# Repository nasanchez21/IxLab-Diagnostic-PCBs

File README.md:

# IxLab-Diagnostic-PCBs
A repository for various hardware diagnostic circuits for testing/maintaining Ix Lab materials

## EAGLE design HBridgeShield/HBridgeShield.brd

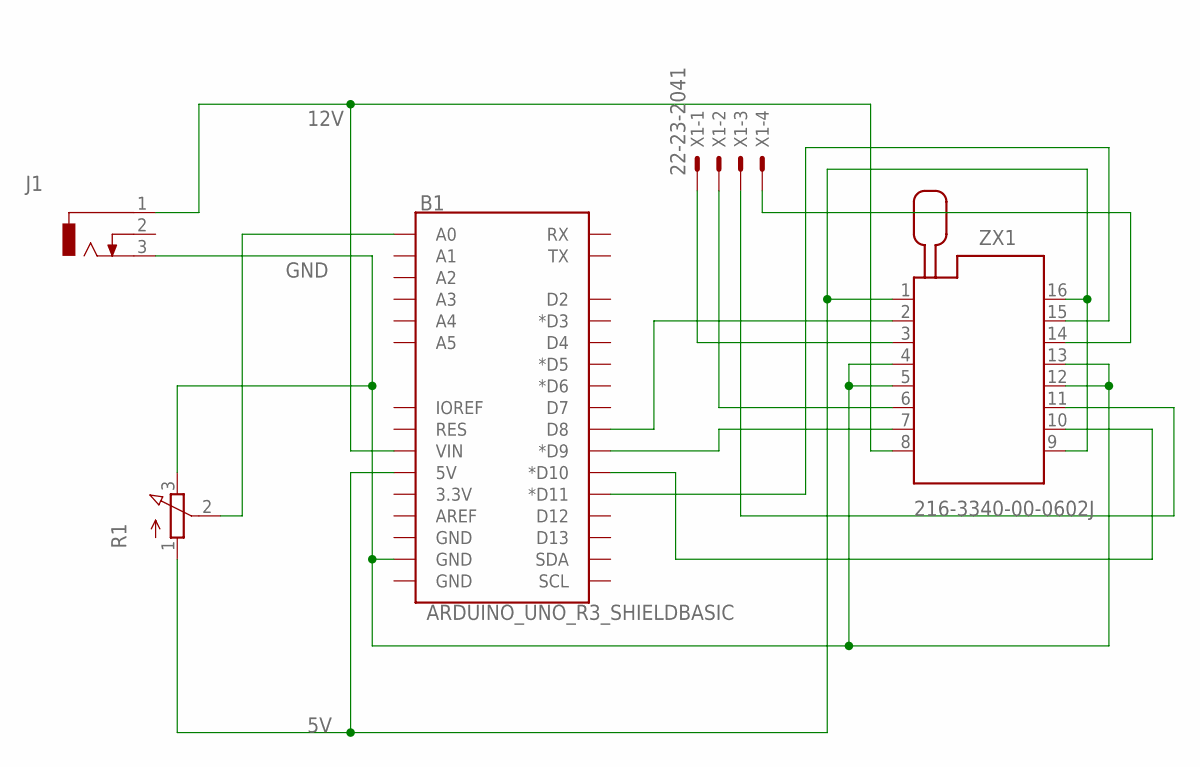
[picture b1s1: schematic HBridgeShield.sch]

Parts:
B1: ARDUINO_UNO_R3_SHIELDBASIC; UNO_R3_SHIELD
J1: DCJ0303
R1: 3RP/1610N
X1: 22-23-2041
ZX1: 216-3340-00-0602J

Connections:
5V: B1.5V, R1.1 (A), ZX1.1, ZX1.9, ZX1.16
12V: B1.VIN, J1.1, ZX1.8
GND: B1.GND@1 (GND), J1.3, R1.3 (E), ZX1.4, ZX1.5, ZX1.12, ZX1.13
unnamed: B1.D9 (*D9), ZX1.7
unnamed: B1.D10 (*D10), ZX1.10
unnamed: B1.D8, ZX1.2
unnamed: B1.D11 (*D11), ZX1.15
unnamed: X1.1, ZX1.3
unnamed: B1.A0, R1.2 (S)
unnamed: X1.2, ZX1.6
unnamed: X1.4, ZX1.14
unnamed: X1.3, ZX1.11

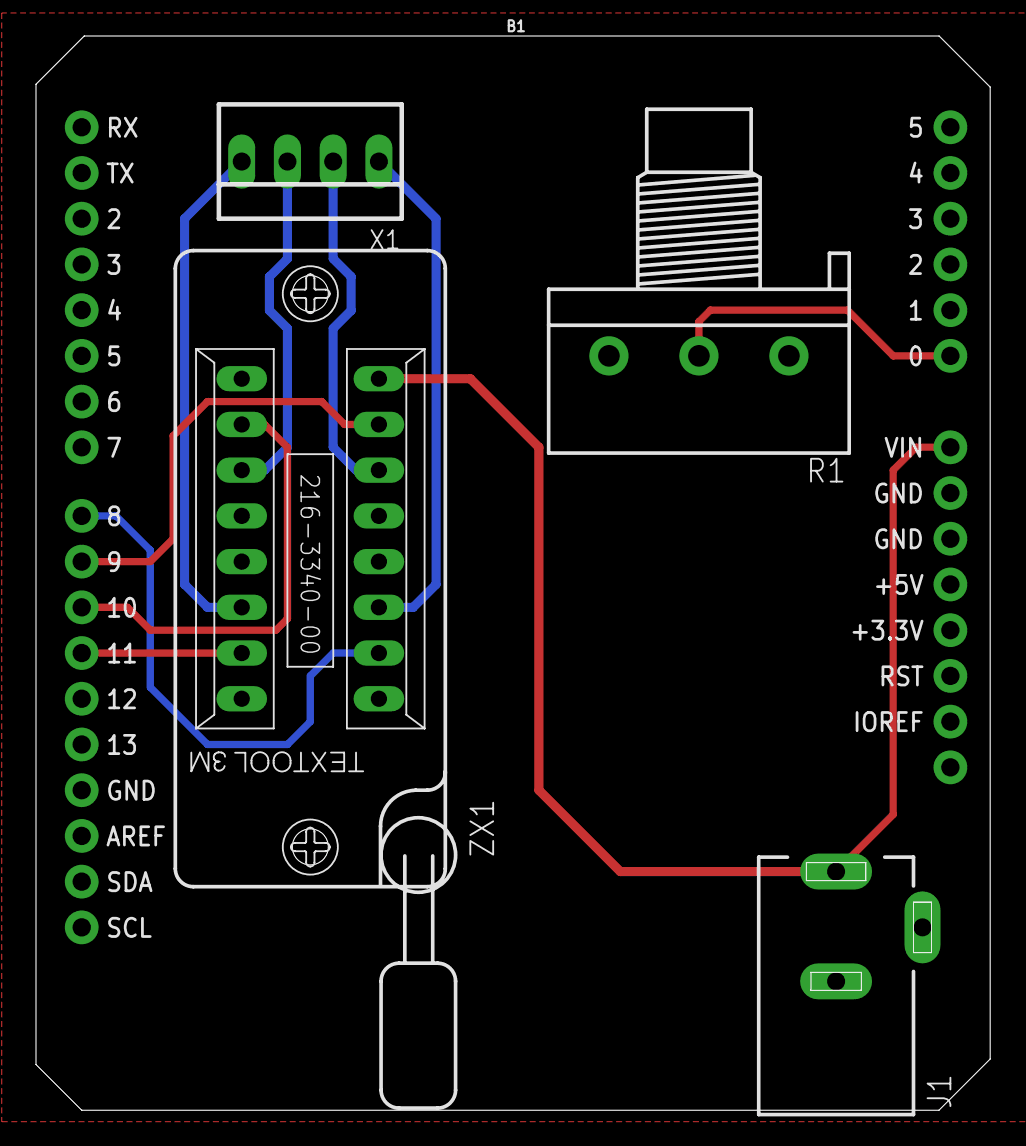
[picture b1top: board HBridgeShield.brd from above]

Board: 2 copper layers, 53.0 x 59.7 mm, 5 parts (0 on the bottom side), 12 nets.

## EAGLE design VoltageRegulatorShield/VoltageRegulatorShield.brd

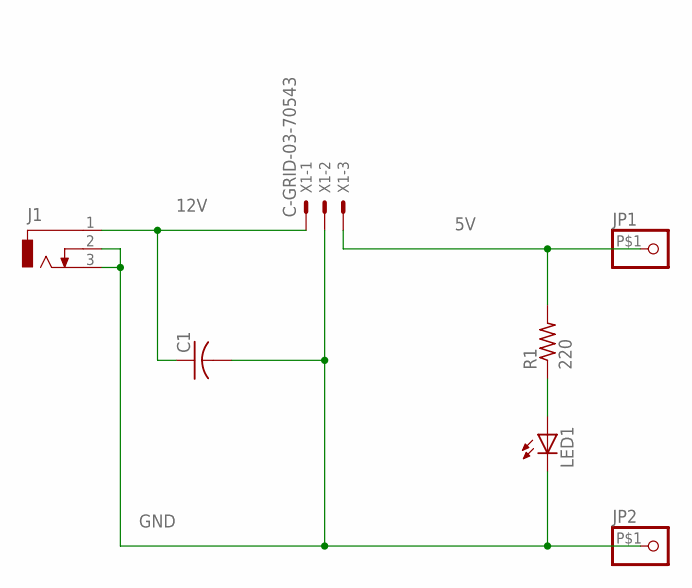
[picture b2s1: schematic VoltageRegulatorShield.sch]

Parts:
C1: C-US025-025X050; C025-025X050
J1: DCJ0303
JP1, JP2: PINHD-1X1-BIGPOGO; 1X1-BIGPOGO
LED1: LED5MM
R1: 220; V234/12
X1: C-GRID-03-70543; 70543-03

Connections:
5V: JP1.P$1, R1.2, X1.3
12V: C1.1, J1.1, X1.1
GND: C1.2, J1.2, J1.3, JP2.P$1, LED1.K (C), X1.2
unnamed: LED1.A, R1.1

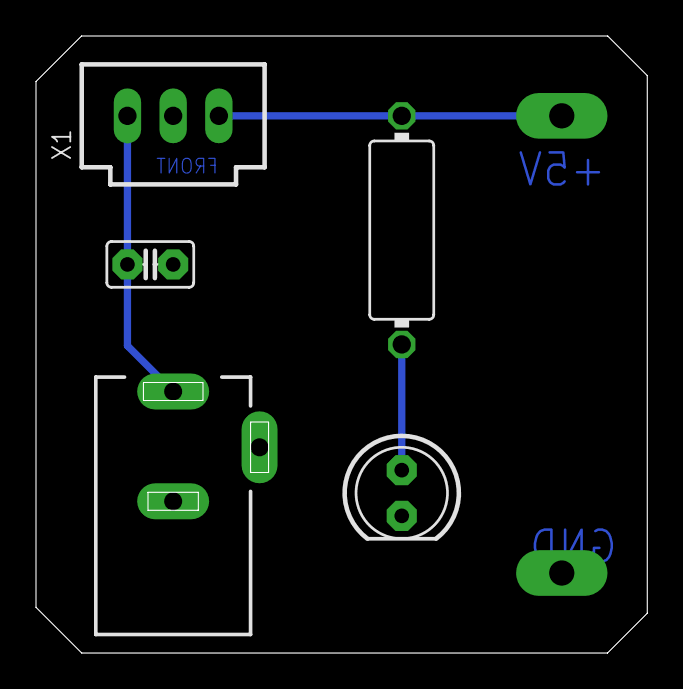
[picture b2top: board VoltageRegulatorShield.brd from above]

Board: 2 copper layers, 34.0 x 34.3 mm, 7 parts (0 on the bottom side), 4 nets.

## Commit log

2019-02-18 Made a test file called hello.txt
2019-02-18 Tristan Armitage has been added to the repository
2019-02-18 Created H-bridge schematic
2019-02-18 Eagle PCB board
2019-02-18 Created Libraries folder for storing downloaded libraries, as well as a README.md file to list ALL libraries used in the project
2019-02-18 First version of Voltage Regulator test board
2019-02-25 No deadly power connection
2019-02-25 Added 12v connection to Arduino board VIN

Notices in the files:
parts and their libraries:
SparkFun-Boards: Licensing: Creative Commons ShareAlike 4.0 International - https://creativecommons.org/licenses/by-sa/4.0
